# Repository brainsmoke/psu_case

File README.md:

# Front panel for MEAN WELL LRS-350-* PSUs

Printed 3mm thick in PETG to offset for material weaknesses due to print orientation.
100% infill (or enough wall thickness so that the slicer doesn't create a zig-zag pattern
for the walls).

TODO: coat it with a UV-blocking paint.

## prints:

* [Main case:](stl/cover.stl)
* [Shield for high voltage wires:](stl/power_shield.stl)

## PCB

* [XT60 'back plane':](pcb/gerb.zip)

## insides:

## type of C14 connector with rocker switch that fits the model:

## Separator to shield input and output power, and neutral from live

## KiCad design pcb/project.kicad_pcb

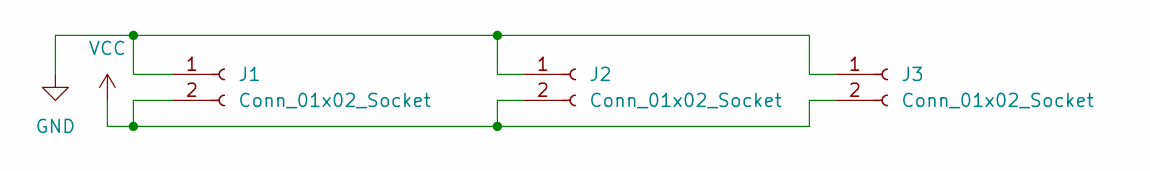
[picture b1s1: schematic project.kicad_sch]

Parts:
J1, J2, J3: Conn_01x02_Socket; AMASS_XT60-F_1x02_P7.20mm_Vertical

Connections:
GND: J1.1, J2.1, J3.1
VCC: J1.2, J2.2, J3.2

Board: 2 copper layers, 3 parts (0 on the bottom side), 2 nets, no tracks yet.

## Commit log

2025-01-29 init
2025-01-29 untested, unfinished
2025-01-31 chamfer xt60 holes
2025-01-31 add stls, unfinished, untested
2025-02-01 fix margin, add separate margin for xt60
2025-02-01 cleanup, add bumps
2025-02-01 update stl, untested, unfinished
2025-02-03 license
2025-02-06 add tests, widen border
2025-02-07 save plastic, add tests
2025-02-07 remove stray file
2025-02-08 adjust power plug margin
2025-02-11 add Makefile
2025-02-11 adjust powerplug latch position
2025-02-11 add readme
2025-02-11 improve readme
2025-02-11 directory reorg
2025-02-11 fix Makefile after move
2025-02-11 readme edit
2025-02-12 fix makefile scad dependencies
2025-02-12 change shape of power plug latches to make it less removable from the inside
2025-02-12 add feet
2025-02-12 add git conffiles
2025-02-14 add separate parameter file
2025-02-14 add power shield image
2025-02-21 fix link typo
2025-03-04 rotate models to print orientation
2025-04-17 small edit in readme
2025-05-07 Use tighter tolerances on PCB for XT60 holes
